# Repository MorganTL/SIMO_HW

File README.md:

## Summary

Single inductor multiple output (SIMO) power supply PCB. feedback control is done on an external STM32G474. Firmware can be found [here](https://github.com/MorganTL/SIMO_SW).

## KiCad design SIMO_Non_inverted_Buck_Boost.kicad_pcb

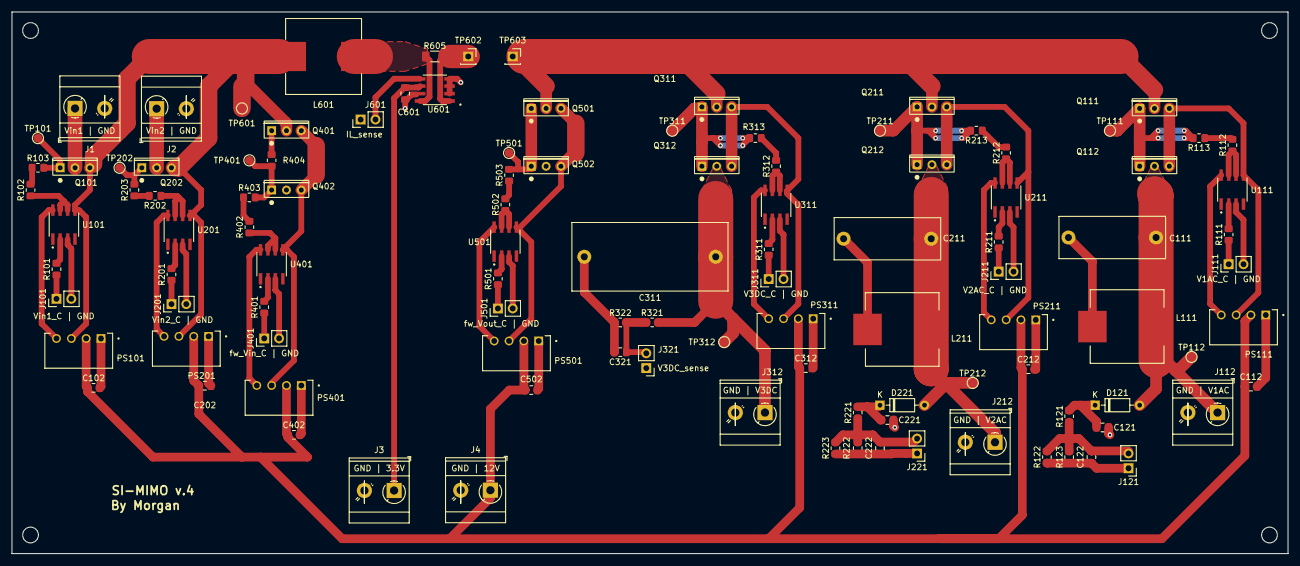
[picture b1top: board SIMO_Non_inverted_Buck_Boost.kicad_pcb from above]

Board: 2 copper layers, 218.4 x 92.7 mm, 110 parts (0 on the bottom side), 73 nets.

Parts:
C102, C112, C121, C122, C202, C212, C221, C222, C312, C321, C402, C502, C601: 100n; C_0805_2012Metric_Pad1.18x1.45mm_HandSolder
C111, C211: 0.22u; C_Rect_L18.0mm_W7.0mm_P15.00mm_FKS3_FKP3
C311: 22u; C_Rect_L26.5mm_W11.5mm_P22.50mm_MKS4
D121, D221: DIODE; D_DO-35_SOD27_P7.62mm_Horizontal_Reverse
J1: Vin1; TerminalBlock_MetzConnect_Type073_RT02602HBLU_1x02_P5.08mm_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
J2: Vin2; TerminalBlock_MetzConnect_Type073_RT02602HBLU_1x02_P5.08mm_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
J3: 3.3V_rail; TerminalBlock_MetzConnect_Type073_RT02602HBLU_1x02_P5.08mm_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
J4: 12V_rail; TerminalBlock_MetzConnect_Type073_RT02602HBLU_1x02_P5.08mm_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
J101: Vin1_MOS_C; PinHeader_1x02_P2.54mm_Vertical
J111: V1AC_MOS_C; PinHeader_1x02_P2.54mm_Vertical
J112: V1_AC; TerminalBlock_MetzConnect_Type073_RT02602HBLU_1x02_P5.08mm_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
J121: V1AC_sens; PinHeader_1x02_P2.54mm_Vertical
J201: Vin2_MOS_C; PinHeader_1x02_P2.54mm_Vertical
J211: V2AC_MOS_C; PinHeader_1x02_P2.54mm_Vertical
J212: V2_AC; TerminalBlock_MetzConnect_Type073_RT02602HBLU_1x02_P5.08mm_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
J221: V2AC_sens; PinHeader_1x02_P2.54mm_Vertical
J311: V3DC_MOS_C; PinHeader_1x02_P2.54mm_Vertical
J312: V3_DC; TerminalBlock_MetzConnect_Type073_RT02602HBLU_1x02_P5.08mm_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
J321: V3DC_sens; PinHeader_1x02_P2.54mm_Vertical
J401: Flywheel_Vin_C; PinHeader_1x02_P2.54mm_Vertical
J501: Flywheel_Vout_C; PinHeader_1x02_P2.54mm_Vertical
J601: IL_sense; PinHeader_1x02_P2.54mm_Vertical
L111, L211: 12u; SRR1260-120M
L601: 6u; L_Wuerth_HCI-1350
PS101, PS111, PS201, PS211, PS311, PS401, PS501: PDSE1-S12-S15-S
Q101, Q111, Q112, Q202, Q211, Q212, Q311, Q312, Q401, Q402, Q501, Q502: IPA083N10N5
R101, R111, R201, R211, R311, R401, R501: 220; R_0805_2012Metric_Pad1.20x1.40mm_HandSolder
R102, R103, R112, R113, R202, R203, R212, R213, R312, R313, R402, R403, R502, R503: 1R - DNP; R_0805_2012Metric_Pad1.20x1.40mm_HandSolder
R121, R221, R321: 100k; R_0805_2012Metric_Pad1.20x1.40mm_HandSolder
R122, R123, R222, R223: 10k; R_0805_2012Metric_Pad1.20x1.40mm_HandSolder
R322: 6k8; R_0805_2012Metric_Pad1.20x1.40mm_HandSolder
R404: 0R - DNP; R_0805_2012Metric_Pad1.20x1.40mm_HandSolder
R605: 3m; R_1206_3216Metric_Pad1.30x1.75mm_HandSolder
TP101, TP111, TP112, TP202, TP211, TP212, TP311, TP312, TP401, TP501, TP601: TestPoint; TestPoint_Pad_D1.5mm
TP602, TP603: TestPoint; PinSocket_1x01_P2.54mm_Vertical
U101, U111, U201, U211, U311, U401, U501: SI8261BAC-C-IS
U601: INA240A4-Q1; SOIC127P600X175-8N

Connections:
+3.3V: C601.1, J3.1, U601.6 (V+)
+12V: C102.1, C112.1, C202.1, C212.1, C312.1, C402.1, C502.1, J4.1, PS101.2 (VIN), PS111.2 (VIN), PS201.2 (VIN), PS211.2 (VIN), PS311.2 (VIN), PS401.2 (VIN), PS501.2 (VIN)
/Flywhell_Vin_MOS_G: Q402.1 (G), R403.2, R404.1, TP401.1
/Flywhell_Vin_MOS_S: PS401.3 (0V), Q401.3 (S), Q402.3 (S), U401.5 (GND)
/Flywhell_Vout_MOS_G: Q501.1 (G), Q502.1 (G), R503.2, TP501.1
/Flywhell_Vout_MOS_S: PS501.3 (0V), Q501.3 (S), Q502.3 (S), U501.5 (GND)
/L_V+: L601.2, R605.1, U601.8 (+)
/L_V-: R605.2, TP602.1, U601.1 (-)
/V1MOS_G: Q111.1 (G), Q112.1 (G), R113.2, TP111.1
/V1MOS_S: PS111.3 (0V), Q111.3 (S), Q112.3 (S), U111.5 (GND)
/V1_AC: C111.1, D121.1 (K), J112.1, L111.1, Q112.2 (D), TP112.1
/V2MOS_G: Q211.1 (G), Q212.1 (G), R213.2, TP211.1
/V2MOS_S: PS211.3 (0V), Q211.3 (S), Q212.3 (S), U211.5 (GND)
/V2_AC: C211.1, D221.1 (K), J212.1, L211.1, Q212.2 (D), TP212.1
/V3MOS_G: Q311.1 (G), Q312.1 (G), R313.2, TP311.1
/V3MOS_S: PS311.3 (0V), Q311.3 (S), Q312.3 (S), U311.5 (GND)
/V3_DC: C311.1, J312.1, Q312.2 (D), R321.2, TP312.1
/Vin1_MOS_G: Q101.1 (G), R103.2, TP101.1
/Vin2_MOS_G: Q202.1 (G), R203.2, TP202.1
/Vin_MOS_S: L601.1, PS101.3 (0V), PS201.3 (0V), Q101.3 (S), Q202.3 (S), Q401.2 (D), TP601.1, U101.5 (GND), U201.5 (GND)
GNDA: C102.2, C111.2, C112.2, C121.2, C122.2, C202.2, C211.2, C212.2, C221.2, C222.2, C311.2, C312.2, C321.2, C402.2, C502.2, C601.2, J1.2, J2.2, J3.2, J4.2, J112.2, J121.1, J212.2, J221.1, J312.2, J321.1, J601.1, L111.2, L211.2, PS101.1 (GND), PS111.1 (GND), PS201.1 (GND), PS211.1 (GND), PS311.1 (GND), PS401.1 (GND), PS501.1 (GND), Q402.2 (D), Q502.2 (D), R122.1, R123.1, R222.1, R223.1, R322.1, U601.2 (GND), U601.3 (REF2), U601.4 (GND), U601.7 (REF1)
unnamed: C121.1, D121.2 (A), R121.2
unnamed: C122.1, J121.2, R121.1, R122.2, R123.2
unnamed: C221.1, D221.2 (A), R221.2
unnamed: C222.1, J221.2, R221.1, R222.2, R223.2
unnamed: C321.1, J321.2, R321.1, R322.2
unnamed: J1.1, Q101.2 (D)
unnamed: J2.1, Q202.2 (D)
unnamed: J101.1, R101.1
unnamed: J101.2, U101.3 (Cathode)
unnamed: J111.1, R111.1
unnamed: J111.2, U111.3 (Cathode)
unnamed: J201.1, R201.1
unnamed: J201.2, U201.3 (Cathode)
unnamed: J211.1, R211.1
unnamed: J211.2, U211.3 (Cathode)
unnamed: J311.1, R311.1
unnamed: J311.2, U311.3 (Cathode)
unnamed: J401.1, R401.1
unnamed: J401.2, U401.3 (Cathode)
unnamed: J501.1, R501.1
unnamed: J501.2, U501.3 (Cathode)
unnamed: J601.2, U601.5
unnamed: PS101.4 (+VOUT), U101.8 (VDD)
unnamed: PS111.4 (+VOUT), U111.8 (VDD)
unnamed: PS201.4 (+VOUT), U201.8 (VDD)
unnamed: PS211.4 (+VOUT), U211.8 (VDD)
unnamed: PS311.4 (+VOUT), U311.8 (VDD)
unnamed: PS401.4 (+VOUT), U401.8 (VDD)
unnamed: PS501.4 (+VOUT), U501.8 (VDD)
unnamed: Q111.2 (D), Q211.2 (D), Q311.2 (D), Q501.2 (D), TP603.1
unnamed: Q401.1 (G), R404.2
unnamed: R101.2, U101.2 (Anode)
unnamed: R102.1, U101.6 (Vo), U101.7 (Vo)
unnamed: R102.2, R103.1
unnamed: R111.2, U111.2 (Anode)
unnamed: R112.1, U111.6 (Vo), U111.7 (Vo)
unnamed: R112.2, R113.1
unnamed: R201.2, U201.2 (Anode)
unnamed: R202.1, U201.6 (Vo), U201.7 (Vo)
unnamed: R202.2, R203.1
unnamed: R211.2, U211.2 (Anode)
unnamed: R212.1, U211.6 (Vo), U211.7 (Vo)
unnamed: R212.2, R213.1
unnamed: R311.2, U311.2 (Anode)
unnamed: R312.1, U311.6 (Vo), U311.7 (Vo)
unnamed: R312.2, R313.1
unnamed: R401.2, U401.2 (Anode)
unnamed: R402.1, U401.6 (Vo), U401.7 (Vo)
unnamed: R402.2, R403.1
unnamed: R501.2, U501.2 (Anode)
unnamed: R502.1, U501.6 (Vo), U501.7 (Vo)
unnamed: R502.2, R503.1

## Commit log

2022-10-10 SIMO with Kelvin designed Isolated Gate driver
2023-02-03 SIMO V4 - Change footprint, current&voltage sensor
2023-09-11 remove backup file
